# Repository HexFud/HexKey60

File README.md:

## HexKey60

Just a custom mechanical keyboard project designed by me

## Specs

- **Layout:** 68 keys, 15 columns x 5 rows matrix, ANSI 65% (up arrow between right Shift and Delete, left/down/right arrows on the bottom row, Fn next to AltGr)
- **Microcontroller:** Raspberry Pi Pico (RP2040), mounted under the spacebar
- **LEDs:** SK6812MINI-E, one per key, same color across the whole board
- **Matrix diodes:** 1N4148, one per switch
- **USB:** routed from the microcontroller (under the spacebar) up to the connector at the top of the case via a Treedix USB-C breakout

## Why the Pico and not something smaller

Originally I was going for something more compact (Orpheus Pico, then XIAO RP2040, then RP2040-Zero) because the standard Pico seemed too bulky to fit between the switches. That problem went away once I moved the microcontroller under the spacebar, where there's way more free space, at that point the regular Pico made more sense, i had space to place it and it has enough pins to fit evry component.

## Matrix

- Rows: GPIO0-GPIO4
- Columns: GPIO5-GPIO19
- Every switch has its own diode to prevent ghosting

## LEDs

Driven via PIO on GPIO21.

LED power comes straight from VBUS (5V), not from the Pico's 3.3V regulator, so the current spikes from 68 LEDs at once don't stress it. Max brightness needs to stay capped in firmware.

## USB

The Pico sits under the spacebar, away from the case edge where the connector needs to come out. D+/D- are hand-wired to test points TP2/TP3 on the back of the Pico (not routed through the PCB), going to a Treedix USB-C breakout mounted in the case. CC1/CC2 on the breakout already have pull-down resistors built in, so they're left unconnected.

## Plate

The plate and the case are fully 3d printed

## Firmware

Live control from a PC over Raw HID (`tastiera68_controller.py`, requires `pip install hidapi`):
- change LED color on the fly (persistent, saved to the Pico's emulated EEPROM)
- remap any key without reflashing (also persistent, saved to a dedicated EEPROM area)

## Building the firmware

### 1. Get QMK

If you don't already have a QMK checkout:

```
git clone https://github.com/qmk/qmk_firmware.git
cd qmk_firmware
```

Follow QMK's own setup guide once (https://docs.qmk.fm/#/newbs_getting_started)
to install the build environment (Python, the ARM toolchain, etc.) if you
haven't done that before — it's a one-time setup per PC.

### 2. Drop this keyboard into the QMK tree

Copy the whole `HexKey60` folder into `qmk_firmware/keyboards/`, so you end
up with:

```
qmk_firmware/
  keyboards/
    HexKey60/
      info.json
      keymaps/
        default/
          keymap.c
          rules.mk
```

### 3. Compile

From the `qmk_firmware` root:

```
qmk compile -kb HexKey60 -km default
```

If everything is set up correctly this produces a file called something
like `HexKey60_default.uf2` in the `qmk_firmware` root folder.

If the build fails on the EEPROM driver lines in `rules.mk`
(`EEPROM_DRIVER` / `WEAR_LEVELING_DRIVER`), check QMK's current docs for the
exact driver name used for RP2040 in your checkout's version — the name has
changed between QMK releases.

### 4. Put the Pico into bootloader mode

The RP2040 shows up as a USB mass-storage drive (`RPI-RP2`) when it's ready
to receive new firmware:

1. Unplug the keyboard.
2. Hold down the **BOOTSEL** button on the Pico (the small white button on
   the board itself).
3. While still holding it, plug the USB cable back in.
4. Let go of the button — a drive called `RPI-RP2` should appear on your
   computer, the same way a USB flash drive would.

### 5. Flash

Just drag and drop the `.uf2` file you built in step 3 onto the `RPI-RP2`
drive. The Pico reboots on its own as soon as the copy finishes, and the
keyboard should now be running your firmware.

If `qmk flash` is set up on your system instead, this also works and does
the copy for you:

```
qmk flash -kb HexKey60 -km default
```

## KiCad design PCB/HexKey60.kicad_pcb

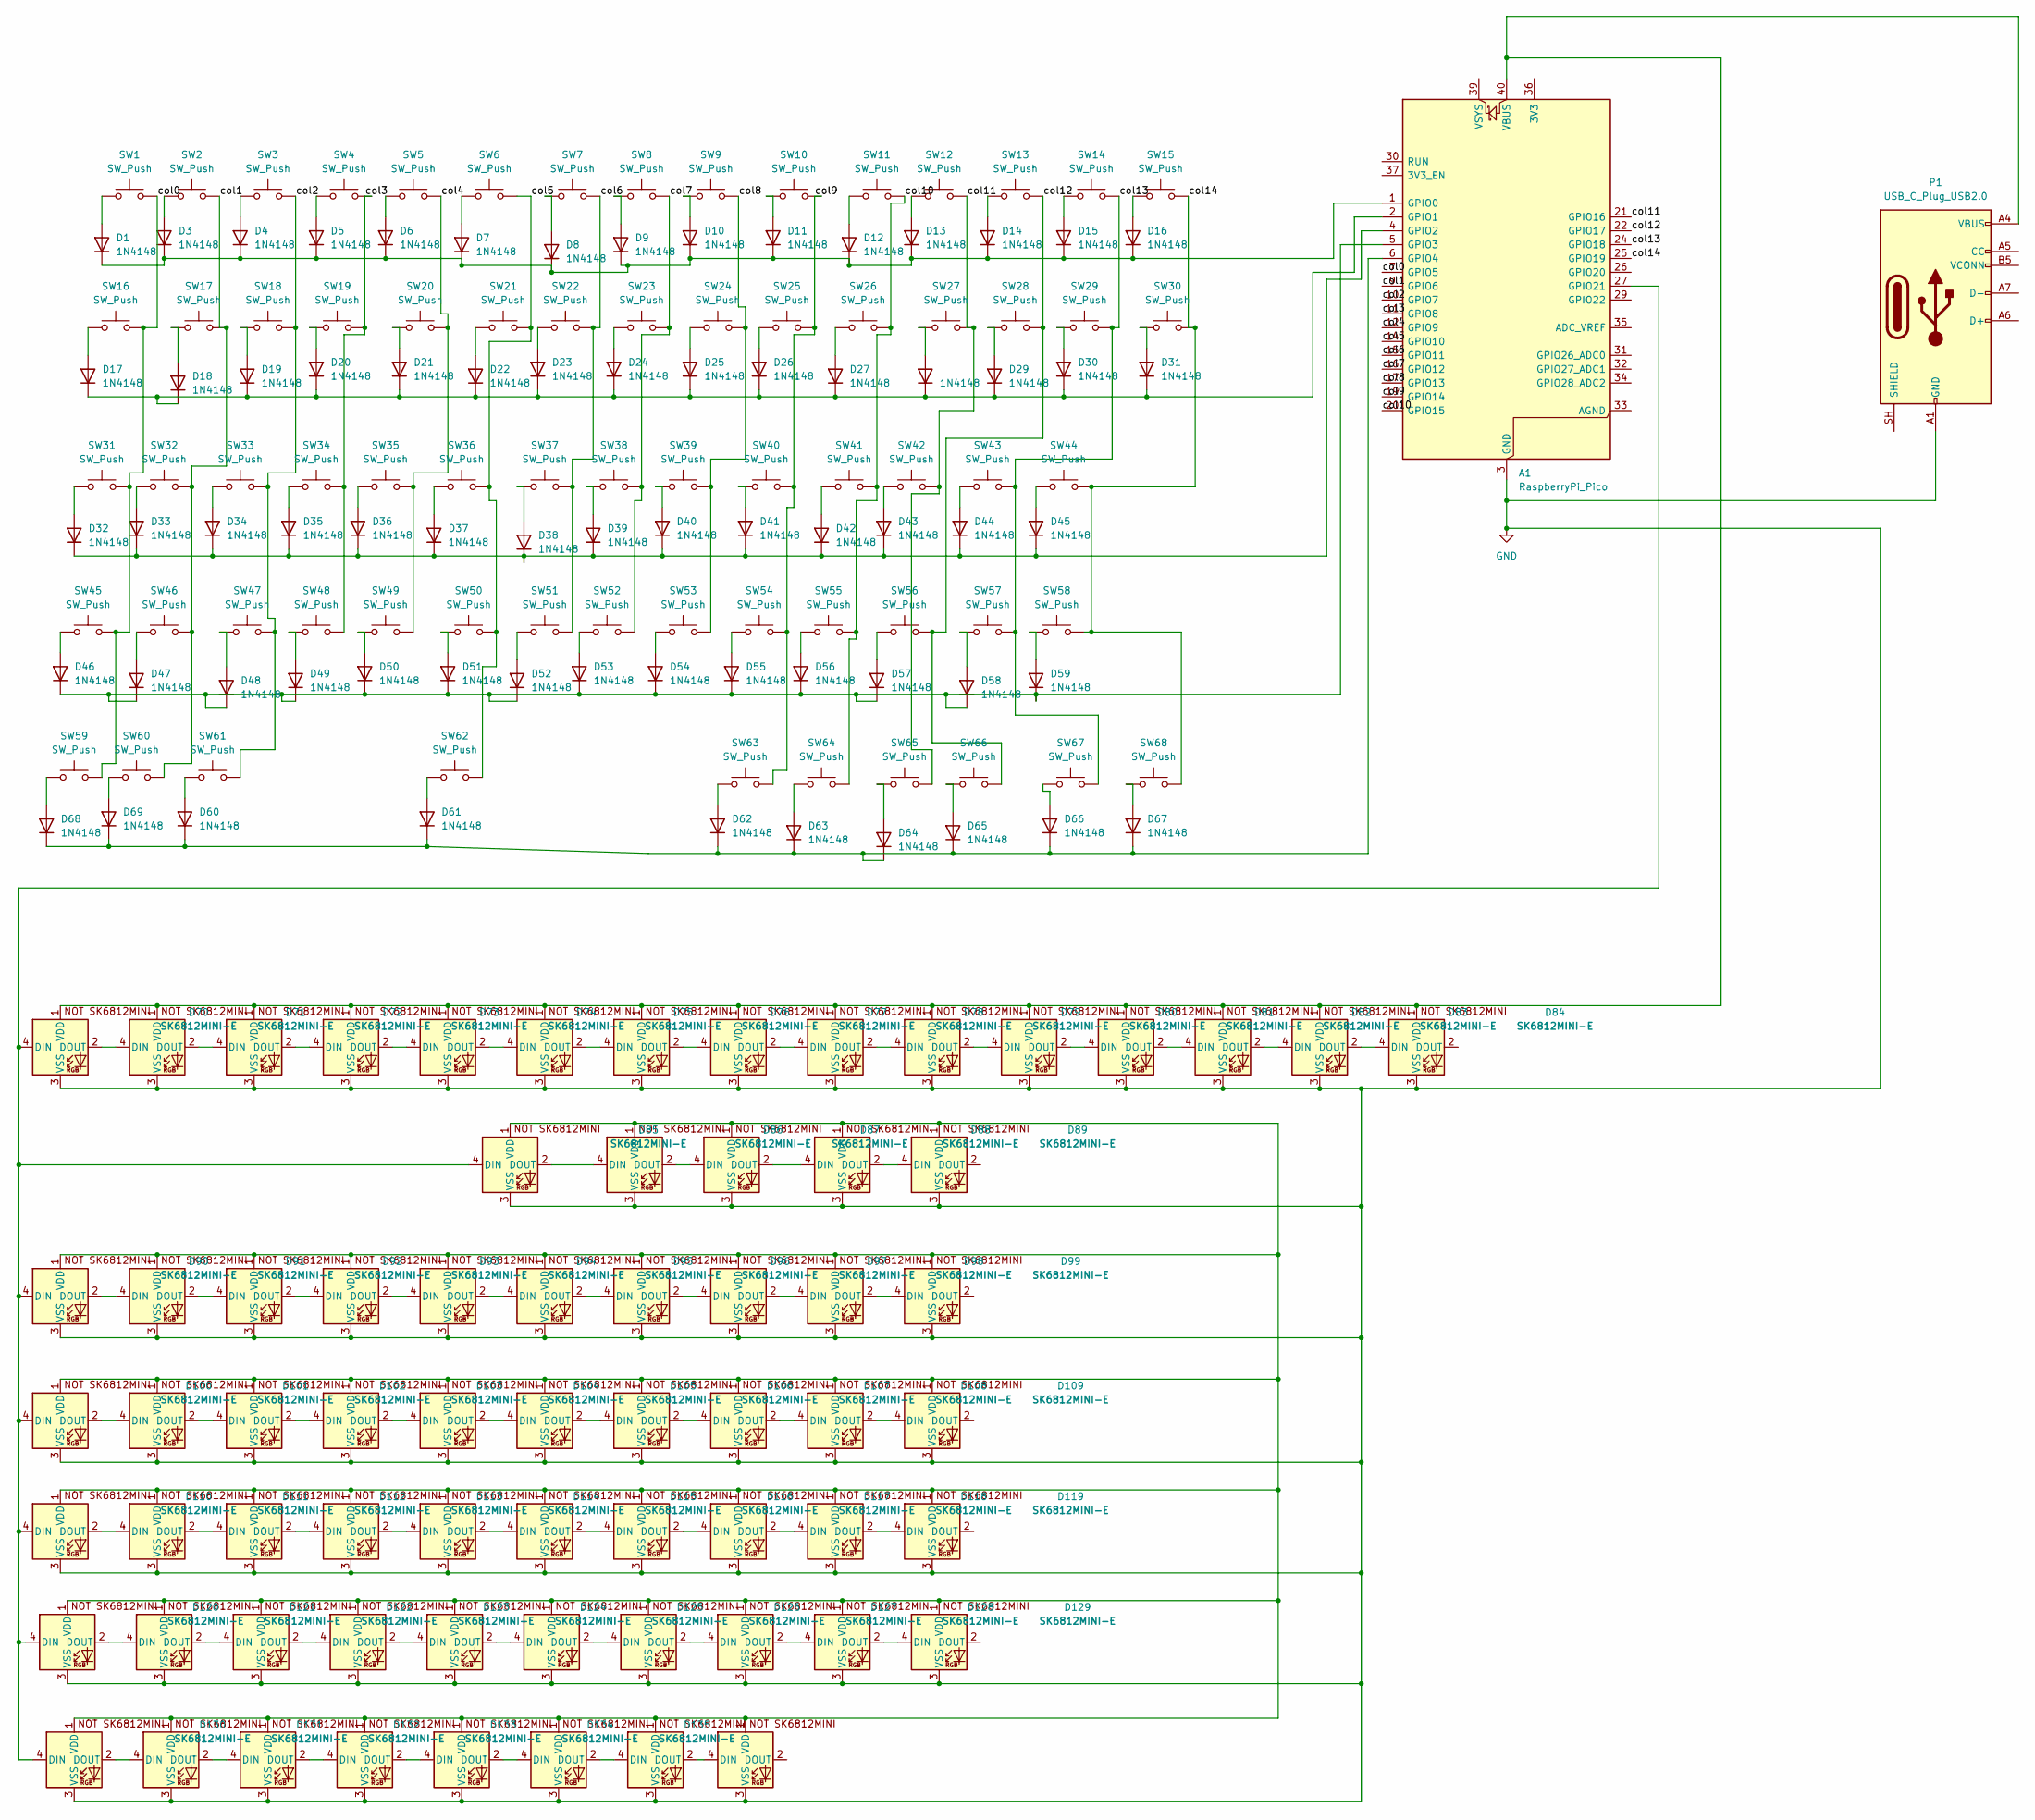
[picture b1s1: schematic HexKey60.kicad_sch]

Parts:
A1: RaspberryPi_Pico; RaspberryPi_Pico_Common_Unspecified
D1, D3, D4, D5, D6, D7, D8, D9, D10, D11, D12, D13, D14, D15, D16, D17, D18, D19, D20, D21, D22, D23, D24, D25, D26, D27, D28, D29, D30, D31, D32, D33, D34, D35, D36, D37, D38, D39, D40, D41, D42, D43, D44, D45, D46, D47, D48, D49, D50, D51, D52, D53, D54, D55, D56, D57, D58, D59, D60, D61, D62, D63, D64, D65, D66, D67, D68, D69: 1N4148; D_DO-35_SOD27_P7.62mm_Horizontal
D70, D71, D72, D73, D74, D75, D76, D77, D78, D79, D80, D81, D82, D83, D84, D85, D86, D87, D88, D89, D90, D91, D92, D93, D94, D95, D96, D97, D98, D99, D100, D101, D102, D103, D104, D105, D106, D107, D108, D109, D110, D111, D112, D113, D114, D115, D116, D117, D118, D119, D120, D121, D122, D123, D124, D125, D126, D127, D128, D129, D130, D131, D132, D133, D134, D135, D136, D137: SK6812MINI-E; SK6812MINI-E_fixed
P1: USB_C_Plug_USB2.0; usbc board
SW1, SW2, SW3, SW4, SW5, SW6, SW7, SW8, SW9, SW10, SW11, SW12, SW13, SW14, SW15, SW16, SW17, SW18, SW19, SW20, SW21, SW22, SW23, SW24, SW25, SW26, SW27, SW28, SW29, SW30, SW31, SW32, SW33, SW34, SW35, SW36, SW37, SW38, SW39, SW40, SW41, SW42, SW43, SW44, SW45, SW46, SW47, SW48, SW49, SW50, SW51, SW52, SW53, SW54, SW55, SW56, SW57, SW58, SW59, SW60, SW61, SW62, SW63, SW64, SW65, SW66, SW67, SW68: SW_Push; SW_Cherry_MX_1.00u_PCB

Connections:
/<NO NET>: A1.7 (GPIO5), SW1.2, SW16.2, SW31.2, SW45.2, SW59.2
/col1: A1.9 (GPIO6), SW2.2, SW17.2, SW32.2, SW46.2, SW60.2
/col2: A1.10 (GPIO7), SW3.2, SW18.2, SW33.2, SW47.2, SW61.2
/col3: A1.11 (GPIO8), SW4.2, SW19.2, SW34.2, SW48.2
/col4: A1.12 (GPIO9), SW5.2, SW20.2, SW35.2, SW49.2
/col5: A1.14 (GPIO10), SW6.2, SW21.2, SW36.2, SW50.2, SW62.2
/col6: A1.15 (GPIO11), SW7.2, SW22.2, SW37.2, SW51.2
/col7: A1.16 (GPIO12), SW8.2, SW23.2, SW38.2, SW52.2
/col8: A1.17 (GPIO13), SW9.2, SW24.2, SW39.2, SW53.2
/col9: A1.19 (GPIO14), SW10.2, SW25.2, SW40.2, SW54.2, SW63.2
/col10: A1.20 (GPIO15), SW11.2, SW26.2, SW41.2, SW55.2, SW64.2
/col11: A1.21 (GPIO16), SW12.2, SW27.2, SW42.2, SW65.2
/col12: A1.22 (GPIO17), SW13.2, SW28.2, SW56.2, SW66.2
/col13: A1.24 (GPIO18), SW14.2, SW29.2, SW43.2, SW57.2, SW67.2
/col14: A1.25 (GPIO19), SW15.2, SW30.2, SW44.2, SW58.2, SW68.2
GND: A1.3 (GND), A1.8 (GND), A1.13 (GND), A1.18 (GND), A1.23 (GND), A1.28 (GND), A1.38 (GND), D70.3 (VSS), D71.3 (VSS), D72.3 (VSS), D73.3 (VSS), D74.3 (VSS), D75.3 (VSS), D76.3 (VSS), D77.3 (VSS), D78.3 (VSS), D79.3 (VSS), D80.3 (VSS), D81.3 (VSS), D82.3 (VSS), D83.3 (VSS), D84.3 (VSS), D85.3 (VSS), D86.3 (VSS), D87.3 (VSS), D88.3 (VSS), D89.3 (VSS), D90.3 (VSS), D91.3 (VSS), D92.3 (VSS), D93.3 (VSS), D94.3 (VSS), D95.3 (VSS), D96.3 (VSS), D97.3 (VSS), D98.3 (VSS), D99.3 (VSS), D100.3 (VSS), D101.3 (VSS), D102.3 (VSS), D103.3 (VSS), D104.3 (VSS), D105.3 (VSS), D106.3 (VSS), D107.3 (VSS), D108.3 (VSS), D109.3 (VSS), D110.3 (VSS), D111.3 (VSS), D112.3 (VSS), D113.3 (VSS), D114.3 (VSS), D115.3 (VSS), D116.3 (VSS), D117.3 (VSS), D118.3 (VSS), D119.3 (VSS), D120.3 (VSS), D121.3 (VSS), D122.3 (VSS), D123.3 (VSS), D124.3 (VSS), D125.3 (VSS), D126.3 (VSS), D127.3 (VSS), D128.3 (VSS), D129.3 (VSS), D130.3 (VSS), D131.3 (VSS), D132.3 (VSS), D133.3 (VSS), D134.3 (VSS), D135.3 (VSS), D136.3 (VSS), D137.3 (VSS), P1.A1 (GND), P1.A12 (GND), P1.B1 (GND), P1.B12 (GND)
unnamed: A1.1 (GPIO0), D1.1 (K), D3.1 (K), D4.1 (K), D5.1 (K), D6.1 (K), D7.1 (K), D8.1 (K), D9.1 (K), D10.1 (K), D11.1 (K), D12.1 (K), D13.1 (K), D14.1 (K), D15.1 (K), D16.1 (K)
unnamed: A1.2 (GPIO1), D17.1 (K), D18.1 (K), D19.1 (K), D20.1 (K), D21.1 (K), D22.1 (K), D23.1 (K), D24.1 (K), D25.1 (K), D26.1 (K), D27.1 (K), D28.1 (K), D29.1 (K), D30.1 (K), D31.1 (K)
unnamed: A1.4 (GPIO2), D32.1 (K), D33.1 (K), D34.1 (K), D35.1 (K), D36.1 (K), D37.1 (K), D38.1 (K), D39.1 (K), D40.1 (K), D41.1 (K), D42.1 (K), D43.1 (K), D44.1 (K), D45.1 (K)
unnamed: A1.5 (GPIO3), D46.1 (K), D47.1 (K), D48.1 (K), D49.1 (K), D50.1 (K), D51.1 (K), D52.1 (K), D53.1 (K), D54.1 (K), D55.1 (K), D56.1 (K), D57.1 (K), D58.1 (K), D59.1 (K)
unnamed: A1.6 (GPIO4), D60.1 (K), D61.1 (K), D62.1 (K), D63.1 (K), D64.1 (K), D65.1 (K), D66.1 (K), D67.1 (K), D68.1 (K), D69.1 (K)
unnamed: A1.27 (GPIO21), D70.4 (DIN), D85.4 (DIN), D90.4 (DIN), D100.4 (DIN), D110.4 (DIN), D120.4 (DIN), D130.4 (DIN)
unnamed: A1.40 (VBUS), D70.1 (VDD), D71.1 (VDD), D72.1 (VDD), D73.1 (VDD), D74.1 (VDD), D75.1 (VDD), D76.1 (VDD), D77.1 (VDD), D78.1 (VDD), D79.1 (VDD), D80.1 (VDD), D81.1 (VDD), D82.1 (VDD), D83.1 (VDD), D84.1 (VDD), P1.A4 (VBUS), P1.A9 (VBUS), P1.B4 (VBUS), P1.B9 (VBUS)
unnamed: D1.2 (A), SW1.1
unnamed: D3.2 (A), SW2.1
unnamed: D4.2 (A), SW3.1
unnamed: D5.2 (A), SW4.1
unnamed: D6.2 (A), SW5.1
unnamed: D7.2 (A), SW6.1
unnamed: D8.2 (A), SW7.1
unnamed: D9.2 (A), SW8.1
unnamed: D10.2 (A), SW9.1
unnamed: D11.2 (A), SW10.1
unnamed: D12.2 (A), SW11.1
unnamed: D13.2 (A), SW12.1
unnamed: D14.2 (A), SW13.1
unnamed: D15.2 (A), SW14.1
unnamed: D16.2 (A), SW15.1
unnamed: D17.2 (A), SW16.1
unnamed: D18.2 (A), SW17.1
unnamed: D19.2 (A), SW18.1
unnamed: D20.2 (A), SW19.1
unnamed: D21.2 (A), SW20.1
unnamed: D22.2 (A), SW21.1
unnamed: D23.2 (A), SW22.1
unnamed: D24.2 (A), SW23.1
unnamed: D25.2 (A), SW24.1
unnamed: D26.2 (A), SW25.1
unnamed: D27.2 (A), SW26.1
unnamed: D28.2 (A), SW27.1
unnamed: D29.2 (A), SW28.1
unnamed: D30.2 (A), SW29.1
unnamed: D31.2 (A), SW30.1
unnamed: D32.2 (A), SW31.1
unnamed: D33.2 (A), SW32.1
unnamed: D34.2 (A), SW33.1
unnamed: D35.2 (A), SW34.1
unnamed: D36.2 (A), SW35.1
unnamed: D37.2 (A), SW36.1
unnamed: D38.2 (A), SW37.1
unnamed: D39.2 (A), SW38.1
unnamed: D40.2 (A), SW39.1
unnamed: D41.2 (A), SW40.1
unnamed: D42.2 (A), SW41.1
unnamed: D43.2 (A), SW42.1
unnamed: D44.2 (A), SW43.1
unnamed: D45.2 (A), SW44.1
unnamed: D46.2 (A), SW45.1
unnamed: D47.2 (A), SW46.1
unnamed: D48.2 (A), SW47.1
unnamed: D49.2 (A), SW48.1
unnamed: D50.2 (A), SW49.1
unnamed: D51.2 (A), SW50.1
unnamed: D52.2 (A), SW51.1
unnamed: D53.2 (A), SW52.1
unnamed: D54.2 (A), SW53.1
unnamed: D55.2 (A), SW54.1
unnamed: D56.2 (A), SW55.1
unnamed: D57.2 (A), SW56.1
unnamed: D58.2 (A), SW57.1
unnamed: D59.2 (A), SW58.1
unnamed: D60.2 (A), SW61.1
unnamed: D61.2 (A), SW62.1
unnamed: D62.2 (A), SW63.1
unnamed: D63.2 (A), SW64.1
unnamed: D64.2 (A), SW65.1
unnamed: D65.2 (A), SW66.1
unnamed: D66.2 (A), SW67.1
unnamed: D67.2 (A), SW68.1
unnamed: D68.2 (A), SW59.1
unnamed: D69.2 (A), SW60.1
unnamed: D70.2 (DOUT), D71.4 (DIN)
unnamed: D71.2 (DOUT), D72.4 (DIN)
unnamed: D72.2 (DOUT), D73.4 (DIN)
unnamed: D73.2 (DOUT), D74.4 (DIN)
unnamed: D74.2 (DOUT), D75.4 (DIN)
unnamed: D75.2 (DOUT), D76.4 (DIN)
unnamed: D76.2 (DOUT), D77.4 (DIN)
unnamed: D77.2 (DOUT), D78.4 (DIN)
unnamed: D78.2 (DOUT), D79.4 (DIN)
unnamed: D79.2 (DOUT), D80.4 (DIN)
unnamed: D80.2 (DOUT), D81.4 (DIN)
unnamed: D81.2 (DOUT), D82.4 (DIN)
unnamed: D82.2 (DOUT), D83.4 (DIN)
unnamed: D83.2 (DOUT), D84.4 (DIN)
unnamed: D85.2 (DOUT), D86.4 (DIN)
unnamed: D86.2 (DOUT), D87.4 (DIN)
unnamed: D87.2 (DOUT), D88.4 (DIN)
unnamed: D88.2 (DOUT), D89.4 (DIN)
unnamed: D90.2 (DOUT), D91.4 (DIN)
unnamed: D91.2 (DOUT), D92.4 (DIN)
unnamed: D92.2 (DOUT), D93.4 (DIN)
unnamed: D93.2 (DOUT), D94.4 (DIN)
unnamed: D94.2 (DOUT), D95.4 (DIN)
unnamed: D95.2 (DOUT), D96.4 (DIN)
unnamed: D96.2 (DOUT), D97.4 (DIN)
unnamed: D97.2 (DOUT), D98.4 (DIN)
unnamed: D98.2 (DOUT), D99.4 (DIN)
unnamed: D100.2 (DOUT), D101.4 (DIN)
unnamed: D85.1 (VDD), D86.1 (VDD), D87.1 (VDD), D88.1 (VDD), D89.1 (VDD), D90.1 (VDD), D91.1 (VDD), D92.1 (VDD), D93.1 (VDD), D94.1 (VDD), D95.1 (VDD), D96.1 (VDD), D97.1 (VDD), D98.1 (VDD), D99.1 (VDD), D100.1 (VDD), D101.1 (VDD), D102.1 (VDD), D103.1 (VDD), D104.1 (VDD), D105.1 (VDD), D106.1 (VDD), D107.1 (VDD), D108.1 (VDD), D109.1 (VDD), D110.1 (VDD), D111.1 (VDD), D112.1 (VDD), D113.1 (VDD), D114.1 (VDD), D115.1 (VDD), D116.1 (VDD), D117.1 (VDD), D118.1 (VDD), D119.1 (VDD), D120.1 (VDD), D121.1 (VDD), D122.1 (VDD), D123.1 (VDD), D124.1 (VDD), D125.1 (VDD), D126.1 (VDD), D127.1 (VDD), D128.1 (VDD), D129.1 (VDD), D130.1 (VDD), D131.1 (VDD), D132.1 (VDD), D133.1 (VDD), D134.1 (VDD), D135.1 (VDD), D136.1 (VDD), D137.1 (VDD)
unnamed: D101.2 (DOUT), D102.4 (DIN)
unnamed: D102.2 (DOUT), D103.4 (DIN)
unnamed: D103.2 (DOUT), D104.4 (DIN)
unnamed: D104.2 (DOUT), D105.4 (DIN)
unnamed: D105.2 (DOUT), D106.4 (DIN)
unnamed: D106.2 (DOUT), D107.4 (DIN)
unnamed: D107.2 (DOUT), D108.4 (DIN)
unnamed: D108.2 (DOUT), D109.4 (DIN)
unnamed: D110.2 (DOUT), D111.4 (DIN)
unnamed: D111.2 (DOUT), D112.4 (DIN)
unnamed: D112.2 (DOUT), D113.4 (DIN)
unnamed: D113.2 (DOUT), D114.4 (DIN)
unnamed: D114.2 (DOUT), D115.4 (DIN)
unnamed: D115.2 (DOUT), D116.4 (DIN)
unnamed: D116.2 (DOUT), D117.4 (DIN)
unnamed: D117.2 (DOUT), D118.4 (DIN)
unnamed: D118.2 (DOUT), D119.4 (DIN)
unnamed: D120.2 (DOUT), D121.4 (DIN)
unnamed: D121.2 (DOUT), D122.4 (DIN)
unnamed: D122.2 (DOUT), D123.4 (DIN)
unnamed: D123.2 (DOUT), D124.4 (DIN)
unnamed: D124.2 (DOUT), D125.4 (DIN)
unnamed: D125.2 (DOUT), D126.4 (DIN)
unnamed: D126.2 (DOUT), D127.4 (DIN)
unnamed: D127.2 (DOUT), D128.4 (DIN)
unnamed: D128.2 (DOUT), D129.4 (DIN)
unnamed: D130.2 (DOUT), D131.4 (DIN)
unnamed: D131.2 (DOUT), D132.4 (DIN)
unnamed: D132.2 (DOUT), D133.4 (DIN)
unnamed: D133.2 (DOUT), D134.4 (DIN)
unnamed: D134.2 (DOUT), D135.4 (DIN)
unnamed: D135.2 (DOUT), D136.4 (DIN)
unnamed: D136.2 (DOUT), D137.4 (DIN)

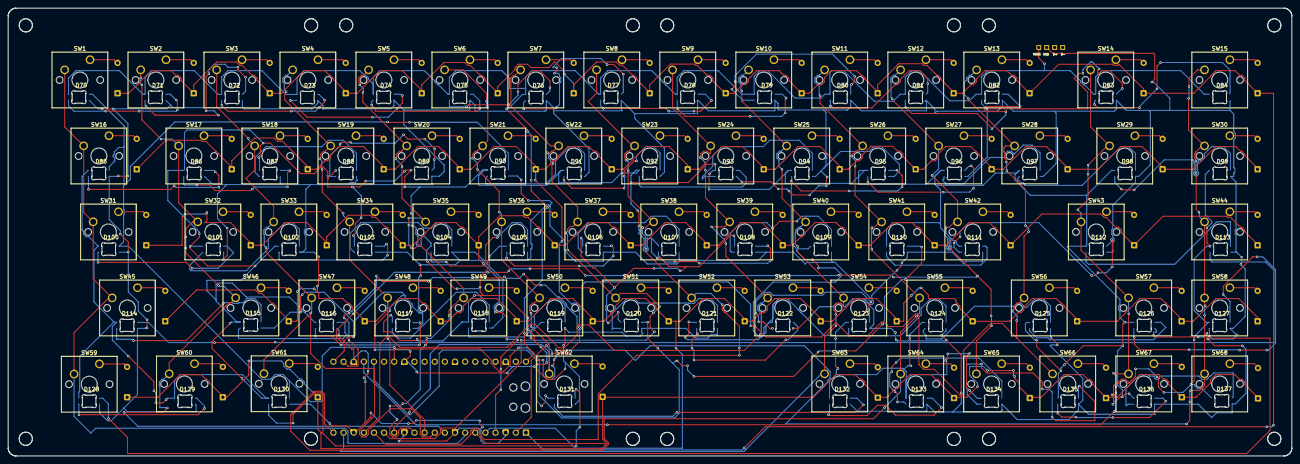
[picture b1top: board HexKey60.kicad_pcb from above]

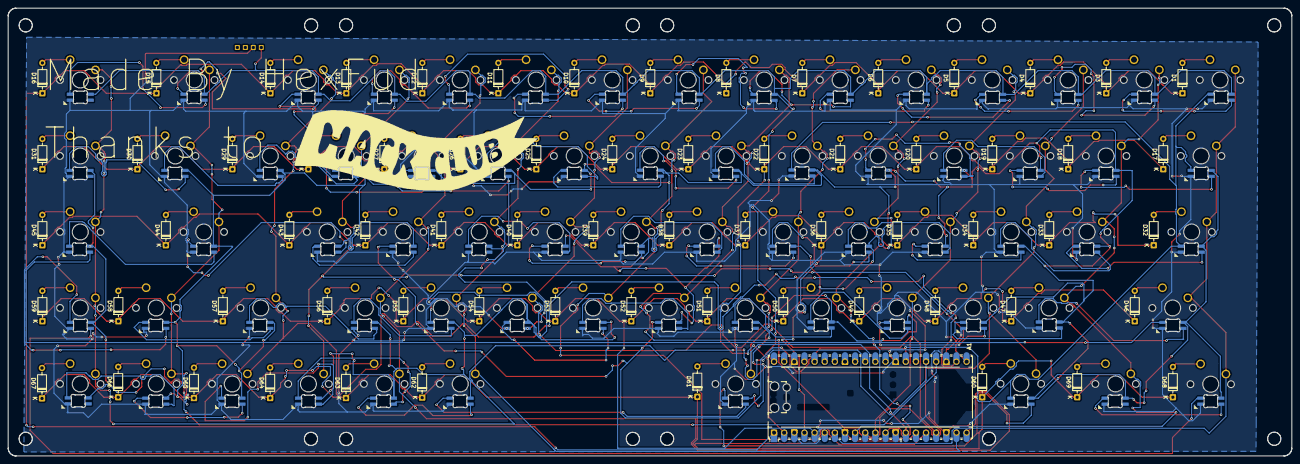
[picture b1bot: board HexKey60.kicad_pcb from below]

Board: 2 copper layers, 321.8 x 112.3 mm, 206 parts (69 on the bottom side), 153 nets.
